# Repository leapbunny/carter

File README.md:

# Carter

Cartridge for gaining access to various hardware features of various LeapFrog Devices. Provides UART through USB (with the CH340) and MicroSD for booting.

## Compatibility
- LeapFrog Didj
- Leapfrog Explorer
- Leapfrog GS
- LeapPad Explorer
- LeapPad2 Explorer

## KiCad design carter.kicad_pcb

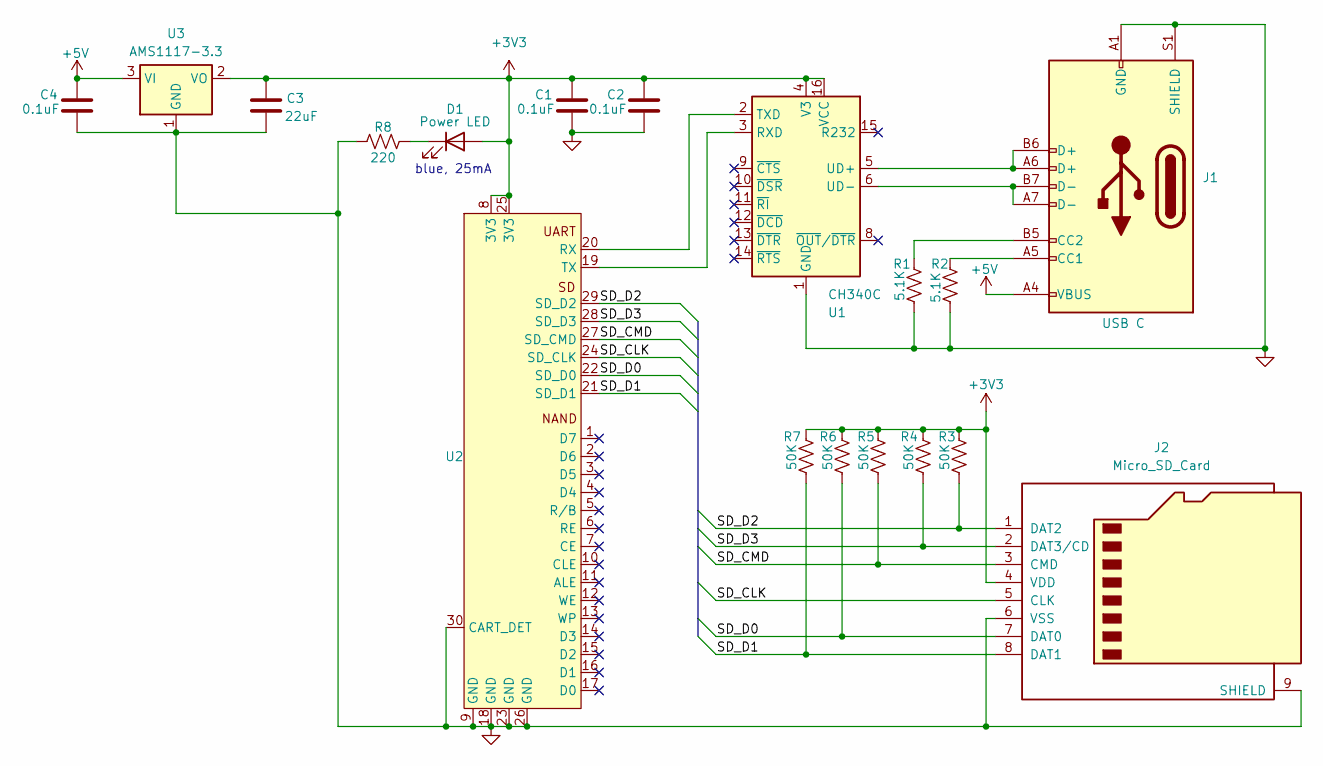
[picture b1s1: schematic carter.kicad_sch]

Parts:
C1, C2, C4: 0.1uF; C_0603_1608Metric; LCSC C14663
C3: 22uF; C_0603_1608Metric; LCSC C59461
D1: Power LED; LED_0603_1608Metric; LCSC C965807
J1: USB C; USB_C_Receptacle_GCT_USB4105-xx-A_16P_TopMnt_Horizontal; LCSC C2988369
J2: Micro_SD_Card; SUNTECH_ST-TF-003A; LCSC C393941
R1, R2: 5.1K; R_0603_1608Metric; LCSC C23186
R3, R4, R5, R6, R7: 50K; R_0805_2012Metric; LCSC C2828840
R8: 220; R_0603_1608Metric; LCSC C4190
U1: CH340C; SOIC-16_3.9x9.9mm_P1.27mm; LCSC C7464026
U2: Cartridge
U3: AMS1117-3.3; SOT-223-3_TabPin2; LCSC C347222

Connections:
+3V3: C1.1, C2.1, C3.1, D1.2 (A), J2.4 (VDD), R3.1, R4.1, R5.1, R6.1, R7.1, U1.4 (V3), U1.16 (VCC), U2.8 (3V3), U2.25 (3V3), U3.2 (VO)
+5V: C4.1, J1.A4 (VBUS), J1.A9 (VBUS), J1.B4 (VBUS), J1.B9 (VBUS), U3.3 (VI)
/SD_CLK: J2.5 (CLK), U2.24 (SD_CLK)
/SD_CMD: J2.3 (CMD), R5.2, U2.27 (SD_CMD)
/SD_D0: J2.7 (DAT0), R6.2, U2.22 (SD_D0)
/SD_D1: J2.8 (DAT1), R7.2, U2.21 (SD_D1)
/SD_D2: J2.1 (DAT2), R3.2, U2.29 (SD_D2)
/SD_D3: J2.2 (DAT3/CD), R4.2, U2.28 (SD_D3)
GND: C1.2, C2.2, C3.2, C4.2, J1.A1 (GND), J1.A12 (GND), J1.B1 (GND), J1.B12 (GND), J1.S1 (SHIELD), J2.6 (VSS), J2.9 (SHIELD), R1.2, R2.2, R8.1, U1.1 (GND), U2.9 (GND), U2.18 (GND), U2.23 (GND), U2.26 (GND), U2.30 (CART_DET), U3.1 (GND)
unnamed: D1.1 (K), R8.2
unnamed: J1.A5 (CC1), R2.1
unnamed: J1.B5 (CC2), R1.1
unnamed: U1.3 (RXD), U2.19 (TX)
unnamed: U1.2 (TXD), U2.20 (RX)
unnamed: J1.A6 (D+), J1.B6 (D+), U1.5 (UD+)
unnamed: J1.A7 (D-), J1.B7 (D-), U1.6 (UD-)

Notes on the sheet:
blue, 25mA

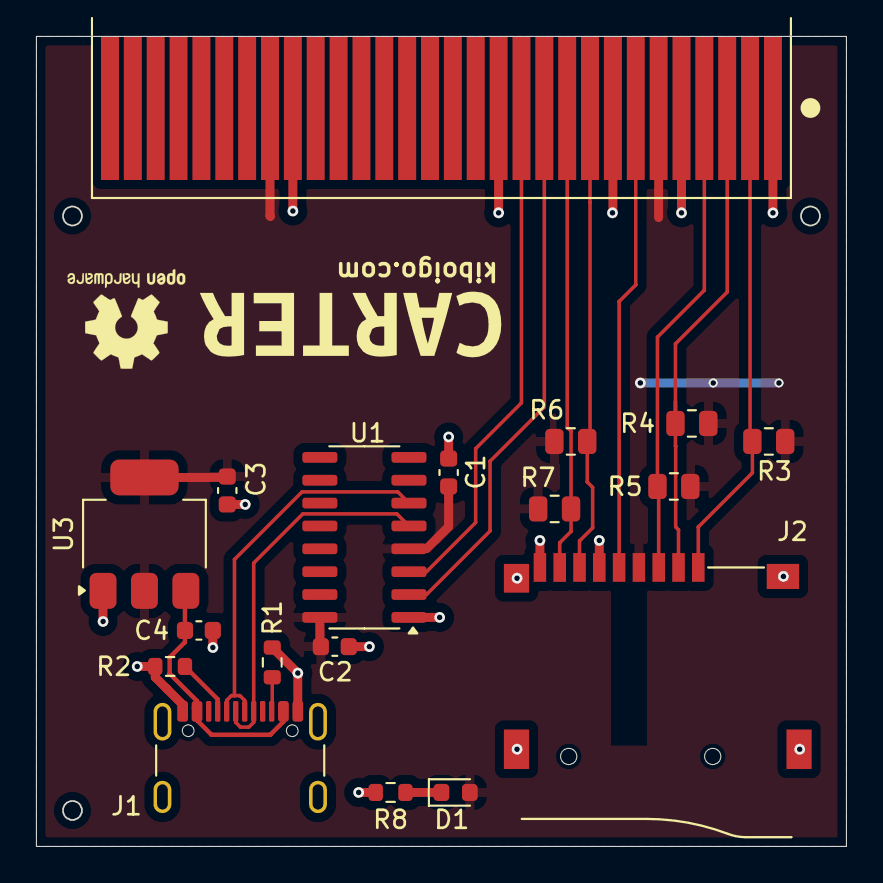
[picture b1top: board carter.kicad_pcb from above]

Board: 2 copper layers, 44.9 x 45.0 mm, 19 parts (0 on the bottom side), 16 nets.

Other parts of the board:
kibuzzard-665A686A: G***; kibuzzard-665A686A

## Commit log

2024-05-07 near v1
2024-05-20 add README
2024-05-22 fix: usb-c connectivity
2024-05-31 redesign with ams1117-3.3
2024-05-31 minimizing ground runs
2024-05-31 slight routing changes
2024-06-01 begin preparing for store
